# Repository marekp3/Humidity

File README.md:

# RTC with humidity and temperature reading

The goal of this project is to create device which will have 3 main functions:
- RTC
- Humidity read
- Temperature read

## Table of content

* [General Info](#general-info)
* [Software](*software)
* [Hardware/PCB](*hardware/pcb)
* [Next Steps](*next-steps)

## General Info

## Software

## Hardware/PCB

## Next Steps

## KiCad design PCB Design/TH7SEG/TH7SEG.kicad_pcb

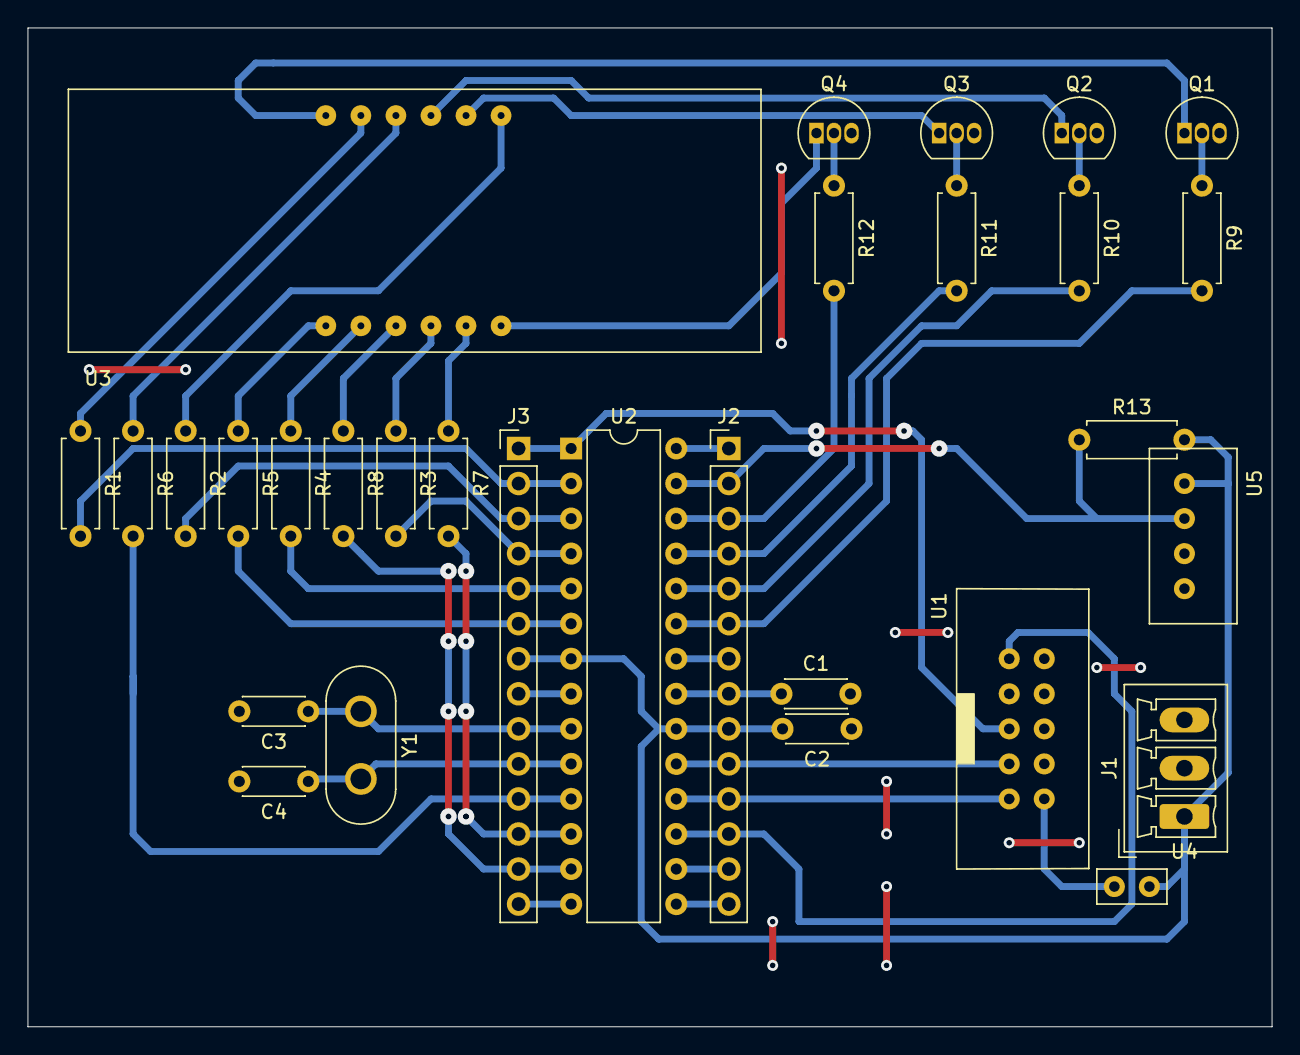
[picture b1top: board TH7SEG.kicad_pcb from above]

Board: 2 copper layers, 90.2 x 72.4 mm, 30 parts (0 on the bottom side), 43 nets.

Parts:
C1, C2: 100nF; C_Disc_D4.3mm_W1.9mm_P5.00mm
C3, C4: 22pF; C_Disc_D4.3mm_W1.9mm_P5.00mm
J1: Conn_01x03_Female; PhoenixContact_MCV_1,5_3-G-3.5_1x03_P3.50mm_Vertical
J2, J3: Conn_01x14_Male; PinHeader_1x14_P2.54mm_Vertical
Q1, Q2, Q3, Q4: BC548; TO-92_Inline
R1, R2, R3, R4, R5, R6, R7, R8: 220; R_Axial_DIN0207_L6.3mm_D2.5mm_P7.62mm_Horizontal
R9, R10, R11, R12: 2k; R_Axial_DIN0207_L6.3mm_D2.5mm_P7.62mm_Horizontal
R13: 1k; R_Axial_DIN0207_L6.3mm_D2.5mm_P7.62mm_Horizontal
U1: IDC10PIN
U2: ATmega8A-PU; DIP-28_W7.62mm
U3: SH5461AW; SH461AW
U4: JumperRast254
U5: AM2302
Y1: Crystal; Crystal_HC50_Vertical

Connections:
Aref: C1.1, J2.8, U2.21
Avcc: C2.2, J1.1, J2.9, J3.7, R13.2, U2.7, U2.20, U4.1, U5.1
GND: C1.2, C2.1, C3.2, C4.2, J1.3, J2.7, J3.8, Q1.3, Q2.3, Q3.3, Q4.3, U1.2, U1.6, U1.7, U1.8, U1.9, U2.8, U2.22, U5.3, U5.4
unnamed: Q1.1, U3.12
unnamed: Q1.2, R9.1
unnamed: Q2.1, U3.9
unnamed: Q2.2, R10.1
unnamed: Q3.1, U3.8
unnamed: Q3.2, R11.1
unnamed: Q4.1, U3.6
unnamed: Q4.2, R12.1
unnamed: R1.1, U3.11
unnamed: R2.1, U3.7
unnamed: R3.1, U3.4
unnamed: R4.1, U3.2
unnamed: R5.1, U3.1
unnamed: R6.1, U3.10
unnamed: R7.1, U3.5
unnamed: R8.1, U3.3
PB0: J3.14, U2.14
PB1: J2.14, U2.15
PB2: J2.13, U2.16
PB3: J2.12, U1.1, U2.17
PB4: J2.11, U1.5, U2.18
PB5: J2.10, U1.4, U2.19
PB6: C3.1, J3.9, U2.9, Y1.1
PB7: C4.1, J3.10, U2.10, Y1.2
PC0: J2.6, R9.2, U2.23
PC1: J2.5, R10.2, U2.24
PC2: J2.4, R11.2, U2.25
PC3: J2.3, R12.2, U2.26
PC4: J2.2, R13.1, U2.27, U5.2
PC5: J2.1, U2.28
PC6: J3.1, U1.3, U2.1
PD0: J3.2, R1.2, U2.2
PD1: J3.3, R2.2, U2.3
PD2: J3.4, R3.2, U2.4
PD3: J3.5, R4.2, U2.5
PD4: J3.6, R5.2, U2.6
PD5: J3.11, R6.2, U2.11
PD6: J3.12, R7.2, U2.12
PD7: J3.13, R8.2, U2.13
VccJ1: U1.10, U4.2

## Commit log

2021-01-07 Initial version
2021-01-10 CRC implemented
    red8bits() - correction in for loop condition. 7 replaced with 8
2021-01-17 correcter 0.00
2021-01-17 hotfix: hum and temp every 5s change
2021-01-17 PCB design added
2021-01-17 clean folder
